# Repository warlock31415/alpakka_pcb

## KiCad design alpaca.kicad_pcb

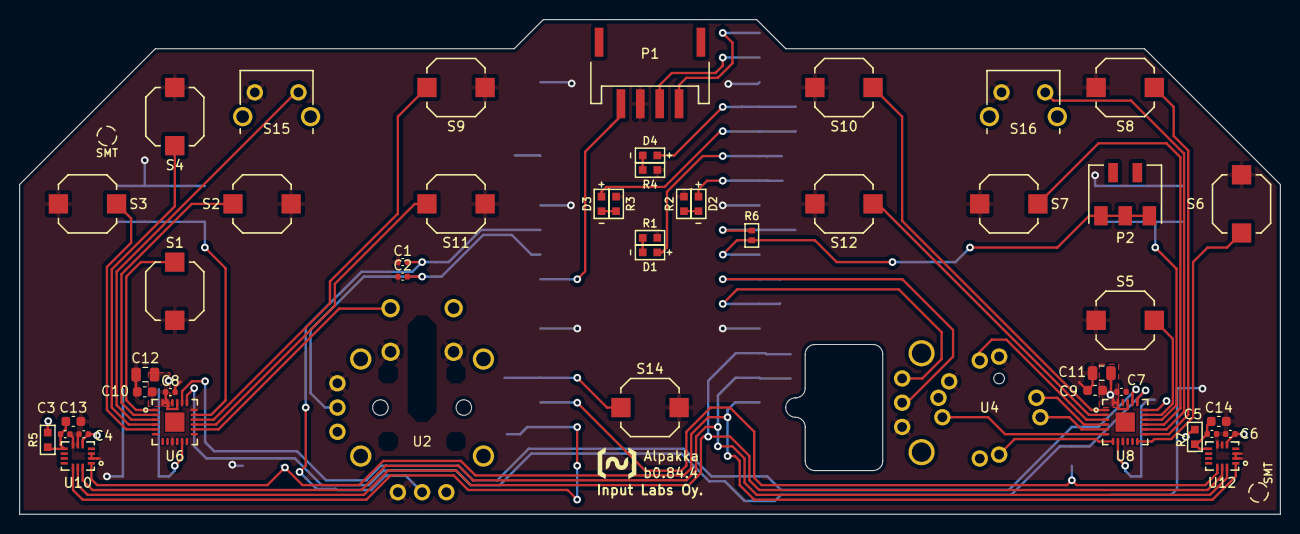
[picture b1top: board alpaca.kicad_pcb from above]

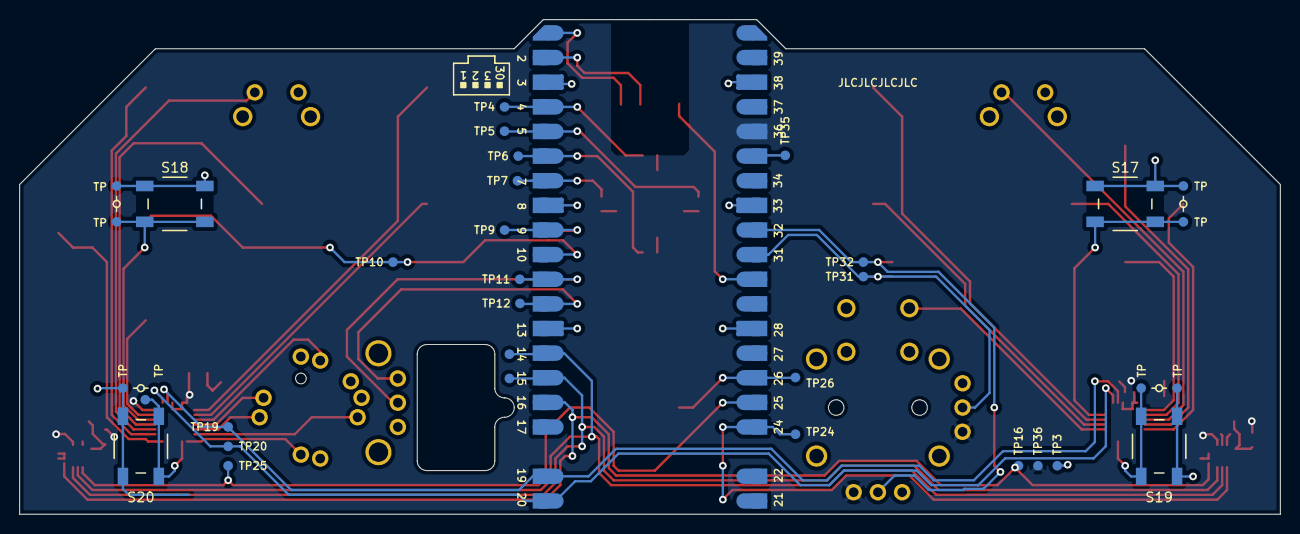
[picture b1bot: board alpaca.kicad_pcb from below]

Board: 2 copper layers, 130.0 x 51.0 mm, 83 parts (34 on the bottom side), 54 nets.

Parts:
C1, C2, C3, C4, C5, C6, C7, C8: C; C_0402_1005Metric
C9, C10, C13, C14: C; C_0603_1608Metric
C11, C12: C; C_0805_2012Metric
D1, D2, D3, D4: Diode; 0603_d
P1: Debug; Boomele_C50137
P2: Endpoint; HRO_BC-25-3P
R1, R2, R3, R4, R5, R7: R; 0603
R6: R6; 0402
S1: down; Alpsalpine_SKPM
S2: right; Alpsalpine_SKPM
S3: left; Alpsalpine_SKPM
S4: up; Alpsalpine_SKPM
S5: a; Alpsalpine_SKPM
S6: b; Alpsalpine_SKPM
S7: x; Alpsalpine_SKPM
S8: y; Alpsalpine_SKPM
S9: select_1; Alpsalpine_SKPM
S10: start_1; Alpsalpine_SKPM
S11: select_2; Alpsalpine_SKPM
S12: start_2; Alpsalpine_SKPM
S14: home; Alpsalpine_SKPM
S15: l1; Alpsalpine_SKHHL
S16: r1; Alpsalpine_SKHHL
S17: l2; Alpsalpine_SKQG
S18: r2; Alpsalpine_SKQG
S19: l4; Alpsalpine_SKQG
S20: r4; Alpsalpine_SKQG
TP3, TP4, TP5, TP6, TP7, TP9, TP10, TP11, TP12, TP14, TP15, TP16, TP19, TP20, TP24, TP25, TP26, TP31, TP32, TP35, TP36, TP101, TP102, TP103, TP104, TP201, TP202, TP203, TP204: Endpoint; Pad_1mm
U1: Raspberry_Pico
U2: Alpsalpine_RKJXV; Alpsalpine_RKJXV122400R
U3: Alpsalpine_EC10E
U4: Alpsalpine_RKJXM; Alpsalpine_RKJXM1015004
U6, U8: NXP_PCAL6416A; QFN24
U10, U12: ST_LSM6; LGA14

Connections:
A0: S1.2, U6.1 (P0)
A1: S2.2, U6.2 (P1)
A2: S15.2, U6.3 (P2)
A3: S4.2, U6.4 (P3)
A4: S3.2, U6.5 (P4)
A9: S19.2, TP204.1, U6.11 (P9)
A12: U2.10 (D), U6.14 (P12)
A13: S11.2, U6.15 (P13)
A14: S9.2, U6.16 (P14)
A15: S17.2, TP202.1, U6.17 (P15)
ADC0: C2.2, TP31.1, U1.31 (ADC_0), U2.2 (ADC0)
ADC1: C1.2, TP32.1, U1.32 (ADC_1), U2.5 (ADC1)
B0: S10.2, U8.1 (P0)
B1: S12.2, U8.2 (P1)
B2: U4.3 (C), U8.3 (P2)
B3: U4.2 (B), U8.4 (P3)
B4: U4.5 (PUSH), U8.5 (P4)
B5: U4.4 (D), U8.6 (P5)
B6: U4.1 (A), U8.7 (P6)
B7: S20.2, TP104.1, U8.8 (P7)
B10: S6.2, U8.12 (P10)
B11: S8.2, U8.13 (P11)
B12: S16.2, U8.14 (P12)
B13: S7.2, U8.15 (P13)
B14: S18.2, TP102.1, U8.16 (P14)
B15: S5.2, U8.17 (P15)
CS0: TP24.1, U1.24 (GP_18), U10.12 (CS)
CS1: TP25.1, U1.25 (GP_19), U12.12 (CS)
GND: C1.1, C2.1, C3.1, C4.1, C5.1, C6.1, C7.2, C8.2, C9.2, C10.2, C11.2, C12.2, C13.2, C14.2, P1.3 (GND), R1.1, R2.1, R3.1, R4.1, S1.1, S2.1, S3.1, S4.1, S5.1, S6.1, S7.1, S8.1, S9.1, S10.1, S11.1, S12.1, S14.1, S15.1, S16.1, S17.1, S18.1, S19.1, S20.1, TP3.1, TP101.1, TP103.1, TP201.1, TP203.1, U1.3 (GND), U1.8 (GND), U1.13 (GND), U1.28 (GND), U1.33 (GND), U1.38 (GND), U2.1 (GND0), U2.4 (GND1), U2.7 (A), U2.9 (C), U3.3 (GND), U4.6 (COM), U4.7 (GND), U6.9 (VSS), U6.18 (ADDR), U8.9 (VSS), U10.2 (SDx), U10.3 (SCx), U10.6 (GNDIO), U10.7 (GND), U12.2 (SDx), U12.3 (SCx), U12.6 (GNDIO), U12.7 (GND)
GP2: D4.2 (A), TP4.1, U1.4 (GP_2)
GP3: D3.2 (A), TP5.1, U1.5 (GP_3)
GP4: D1.2 (A), TP6.1, U1.6 (GP_4)
GP5: D2.2 (A), TP7.1, U1.7 (GP_5)
GP6: R6.1, TP9.1, U1.9 (GP_6)
GP7: P2.1, R6.2, TP10.1, U1.10 (GP_7)
GP8: TP11.1, U1.11 (GP_8), U3.2 (B)
GP9: TP12.1, U1.12 (GP_9), U3.1 (A)
GP20: S14.2, TP26.1, U1.26 (GP_20)
I2C_SCL: TP20.1, U1.20 (GP_15), U6.19 (SCL), U8.19 (SCL)
I2C_SDA: TP19.1, U1.19 (GP_14), U6.20 (SDA), U8.20 (SDA)
unnamed: C3.2, C13.1, R5.1, U10.8 (VDD)
unnamed: C5.2, C14.1, R7.1, U12.8 (VDD)
unnamed: D1.1 (K), R1.2
unnamed: D2.1 (K), R2.2
unnamed: D3.1 (K), R3.2
unnamed: D4.1 (K), R4.2
RUN: P1.4 (RUN), U1.30 (RUN)
SPI_CK: TP14.1, U1.14 (GP_10), U10.13 (SCL), U12.13 (SCL)
SPI_RX: TP16.1, U1.16 (GP_12), U10.1 (SDO), U12.1 (SDO)
SPI_TX: TP15.1, U1.15 (GP_11), U10.14 (SDA), U12.14 (SDA)
UART_RX: P1.2 (UART_RX), U1.2 (GP_1)
UART_TX: P1.1 (UART_TX), U1.1 (GP_0)
VCC: C4.2, C6.2, C7.1, C8.1, C9.1, C10.1, C11.1, C12.1, R5.2, R7.2, TP36.1, U1.36 (3V3_OUT), U2.3 (VCC0), U2.6 (VCC1), U6.21 (VDD), U6.23 (VDDBUS), U6.24 (RESET), U8.18 (ADDR), U8.21 (VDD), U8.23 (VDDBUS), U8.24 (RESET), U10.5 (VDDIO), U12.5 (VDDIO)
VCCA: TP35.1, U1.35 (ADC_VREF)

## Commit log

2022-12-09 Saving with unpoured GND planes
2022-12-09 Adding hierarchical sheets and bus definitions
